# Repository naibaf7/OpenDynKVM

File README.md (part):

<p align="center">
  <picture>
    <source media="(prefers-color-scheme: dark)" srcset="branding/opendynkvm-logo-on-dark.svg">
    
  </picture>
</p>

<h2 align="center">Product page: <a href="https://smartapes.no/opendynkvm/">https://smartapes.no/opendynkvm/</a></h2>

# OpenDynKVM

An open-source USB KVM switch for two PCs that switches in under a millisecond. Each PC is permanently connected to a
keyboard, mouse and aux devices emulated by the KVM ("persistent emulation"), so a switch only changes where the
reports go: no PC sees a disconnect, nothing re-enumerates, and High-Speed USB on the PC side adds about 0.1 ms of
latency. Devices that cannot be emulated (webcams, flash drives) go straight to a PC in passthrough mode. Keyboards
without their own remapping can be remapped on the KVM with the Vial app.

- **Back:** USB-C to PC1, USB-C to PC2, USB-C power/service port (optional power, firmware recovery).
- **Front:** four USB-A ports, Keyboard, Mouse, Aux 1 and Aux 2 (boards before 0.19.0 have three, without Aux 1); a
  mechanical key (tap = switch PC) with an RGB LED; status LEDs per PC and per port.
- **Inside:** an RP2354B (USB host for the front ports, all switching logic), two AT32F405 (one High-Speed USB device per
  PC), three USB 2.0 hubs and a 1:3 analog USB switch per front port but Aux 1, which has no passthrough.

**Status (2026-11-14):** the first boards, hardware 0.12.0, run firmware 0.1.19. Hardware 0.19.0, with the fixes from
their bring-up, a fourth front port and the ESP32-MINI-1 module (2026-11-25), is designed but not ordered yet; one
firmware serves both. What has been verified on a board and what has not:
[DEVELOPMENT.md](DEVELOPMENT.md#bring-up-status).

## Documentation

| | |
|---|---|
| [`specs.md`](specs.md) | What the KVM does, in numbers |
| [`design.md`](design.md) | How the hardware works and why: block diagram, port modes, components, power, PCB |
| [`software.md`](software.md) | How the firmware and the host software work: protocols, updates, Vial, Bluetooth, screen hop |
| [`DEVELOPMENT.md`](DEVELOPMENT.md) | Building the firmware and the host software, changing the board, bring-up status |
| [`hardware/jlcpcb.md`](hardware/jlcpcb.md) | Ordering the board from JLCPCB |
| [`hardware/errata.md`](hardware/errata.md) | Faults of boards already ordered, their workarounds and fixes |
| [`qualified_hardware.md`](qualified_hardware.md) | Mice, keyboards, gamepads and hosts that have been tried, by hardware type |

## Getting a board

There are no boards for sale. The board is ordered assembled from JLCPCB with the files in [`hardware/`](hardware/):
[hardware/jlcpcb.md](hardware/jlcpcb.md) lists every setting of the quote form. Only the MX key switch is plugged into
its socket by hand. The Bluetooth module is optional (boards from 0.16.0): a BOM without it is included. A board
without it can use a small ESP32-C3 board with a USB port (the chip's own, as most have) on a front port instead: the
KVM programs it with the module's firmware when it is new or erased, and that port then serves the wireless hosts
rather than a PC ([software.md §4.13](software.md)).

A 3D-printable case (a tray, a lid with the logo, four spacers and four M3 screws) is in
[`hardware/case/`](hardware/case/), with how to print and assemble it.

## First start of a new board

The chips arrive blank. A USB-C cable is all it takes ([design.md §10](design.md)):

1. Connect a computer to the **PWR/SERVICE** port. A blank RP2354B starts its ROM bootloader and an `RP2350` drive
   appears. (On a board that has firmware, hold the pinhole button while plugging in.)
2. In the app's *Firmware* page, *Set up* (or `odkvmctl update`): it recognises the new board and installs the shipped
   `kvm-first.uf2`. By hand: copy `kvm-first.uf2` (from a release, or built with `cargo xtask dist`) onto the drive.
   The RP2354B restarts with the firmware.
3. It programs both AT32F405s over their SPI links: a few seconds, during which the PC-side hubs are held in reset.
4. The **self-test** runs: one white LED walks along the chain, then for 5 s each LED shows its result, green = passed,
   blinking red = failed (PC LEDs: that PC's link, hub and AT32F405; port LEDs: the port's power switch; key LED: Hub-0
   and the power readings). `odkvmctl status` shows failures in words.
5. Connect PC1 and PC2 to the rear USB-C ports and the devices to the front. Either PC's port can power the KVM, but a
   USB 2.0 port (500 mA) is not enough; a USB-C charger on PWR/SERVICE covers everything ([design.md §6](design.md)).

**Firmware updates** later come from either PC: the *Firmware* page's *Install*, or `odkvmctl update` (both take the
firmware shipped with the app unless given a file or a release's folder), then press the KVM's key when its LED pulses
white. The new image runs on trial and the old one comes back by itself if it fails; the AT32F405s are reprogrammed
automatically when their image changed. A board whose firmware doesn't come up takes the same over PWR/SERVICE: the
pinhole held while plugging in (or `odkvmctl reboot bootloader`), then *Install* on the page's bootloader card, or
`odkvmctl update` with no KVM on a PC port; or copy `kvm-rp2354.uf2` onto the drive by hand.

The app and the firmware go together: a KVM whose firmware is another version than the app's gets only the update
(every page says so, the Firmware page installs the firmware that came with the app, and `odkvmctl` refuses every
command but `update`).

### Install the host software

`opendyn-kvm` (window and tray icon) and `odkvmctl` (command line) control the KVM from either PC.

- **Windows:** run `OpenDynKVM-Setup-<version>.exe`. It installs for the current user, without administrator rights,
  to `%LOCALAPPDATA%\Programs\OpenDynKVM` (both programs are there), with a Start menu entry and an uninstaller under
  Apps. "Start with Windows, in the tray" is ticked by default. The installer is not code-signed yet, so SmartScreen
  asks once ("More info" → "Run anyway").
- **Debian, Ubuntu:** `sudo apt install ./opendyn-kvm_<version>_amd64.deb`.
  **Fedora, openSUSE:** `sudo dnf install ./opendyn-kvm-<version>-1.x86_64.rpm` (or `zypper install`).
  Both install the programs, a menu entry and the udev rule that gives the logged-in user access to the KVM and to the
  monitors' DDC/CI, and load the `i2c-dev` module (now and at every boot).
  The packages are not signed yet. Where RPM refuses unsigned packages ("does not verify: no signature", RPM 6 on
  recent Fedora), install it with `sudo rpm -U --nosignature ./opendyn-kvm-<version>-1.x86_64.rpm`.
- **Start with the system:** Settings → This computer → "Start with the system, in the tray" in `opendyn-kvm` (a
  setting of this computer and user: the Run entry on Windows, `~/.config/autostart` on Linux). `opendyn-kvm --tray`
  starts with the tray icon only; starting the program again while it runs opens its window. On GNOME the tray icon
  needs the AppIndicator extension; without it the window opens instead.
- **From source on Linux**, install the udev rule and the module setting once yourself
  ([DEVELOPMENT.md](DEVELOPMENT.md#build-and-test)).
- **Without a KVM yet:** while none is connected, `opendyn-kvm` offers *Try with a simulated KVM*. Everything acts on
  a made-up KVM, except what doesn't need one: the monitors set up on the Displays page really switch inputs (DDC/CI)
  when the simulated KVM switches, and Screen hop can detect this computer's screens. Monitors set up this way stay
  set up for the real KVM. *Leave the simulator* (or *Use it*, once a KVM is plugged in) goes back to it.

Vial (vial.rocks in the browser, or the Vial app) opens the KVM's Vial interface itself, as the logged-in user. The
packages' udev rule covers it, matched by its interface name "OpenDynKVM Vial" (firmware 0.1.10 on), and opens only that
interface. Without it the interface is root's, and Vial waits at "connecting to device" for good. Vial's own rule
(`59-vial.rules`, from the [Vial manual](https://get.vial.today/manual/linux-udev.html)) works too, matching the KVM by
the `vial:f64c2b3c` in its serial number, but it opens every HID interface of the KVM to the logged-in user, the
keyboard ones included.

Windows needs no drivers.

## Using the KVM

- **Switch PCs:** tap the key on the KVM, double-tap Scroll Lock (the default hotkey, invisible to both PCs), or
  `odkvmctl switch pc1|pc2|toggle`. Keys held during a switch are released on the old PC and stay hidden on the new one
  until you let go.
- **Hotkeys:** a list of up to 16, each an action and its hotkey, on the GUI's Keyboard page (**Add hotkey**, the
  action, the hotkey, **Apply**; × removes one) or with `odkvmctl hotkey`. Out of the box there is one: double-tap
  Scroll Lock toggles the PC. Actions: toggle PC, next / previous host (PC1, PC2, then the Bluetooth hosts that are
  connected), select a host (PC1, PC2, Bluetooth host 1–4), next / previous profile, select a profile (0–7), cycle the
  Aux 2 port's mode. On the command line: `odkvmctl hotkey add select-pc1 ctrl+alt+1`, `odkvmctl hotkey` lists them,
  `odkvmctl hotkey set 2 none`, `odkvmctl hotkey remove 2`. Or press a hotkey instead of typing it: `learn` in place of
  it, or **Learn** on the Keyboard page, then the hotkey on the KVM's keyboard within 10 s. The KVM itself reads the
  keys, so it learns exactly what it will recognise, and they reach neither PC meanwhile (Alt+F4 closes nothing). It
  works from the active PC, with a keyboard in Auto, Normalized or Mirrored mode; one in Passthrough goes straight to
  the PC, so no hotkey works on it.
- **Profiles:** up to eight. A profile sets every device's mode and where its input goes, all at once: the three
  front ports' and the paired Bluetooth devices'. A long press (1 s) on the KVM's key selects the next one. The KVM powers up in profile 0, as it loses power only when both PCs are off; `odkvmctl config set
  remember-profile on` makes it power up in the profile last active. Out of the box, profile 0 *work* runs every port
  in auto (emulated, instant switching) and profile 1 *gaming* runs every port in passthrough (the real devices, about
  1 s per switch). `odkvmctl profile` lists them,
  `odkvmctl profile next|1|gaming` selects one, `odkvmctl profile 1 name games` renames it,
  `odkvmctl profile 1 mouse mirrored` changes a mode, `odkvmctl profile 1 other passthrough pc2` a mode and where it
  goes, and `odkvmctl config set profiles 1-8` sets how many are in use. The GUI has them on the Ports page (a tab per
  profile, a row per device with its mode and where its input goes) and in the sidebar. In passthrough the KVM can't see the keyboard, so the hotkey
  doesn't switch there: use the key or the software.
- **The key's actions:** `odkvmctl config set key-tap|key-long toggle-pc|next-profile|aux2-port|none` and
  `odkvmctl config set long-press-ms 800-3000` (GUI: Keyboard page). By default a tap switches PCs and a 1 s long
  press selects the next profile.
- **Port modes** (`odkvmctl port keyboard|mouse|aux1|aux2 mode <mode>`, which changes the active profile; Aux 1 takes
  every mode but `passthrough`):

  | Mode | What the PCs see | Use it for |
  |---|---|---|
  | `auto` (default) | picks one of the below per device | almost everything |
  | `normalized` | the KVM's own keyboard/mouse | ordinary keyboards and mice; switching is seamless |
  | `mirrored` | the device's own HID interfaces, copied | extra buttons, dials, gamepads |
  | `identity` | as mirrored, plus the device's VID/PID and name | the device maker's own configuration software on the active PC |
  | `passthrough` | the real device on that PC's hub | webcams, storage, firmware updates of a device |
  | `off` | nothing: its input goes nowhere | a device kept plugged in but not wanted in this profile |

  Mirrored devices share 3 USB endpoints, one per HID interface (2 with Vial on). While the keyboard and the mouse
  are both mirrored, the KVM gives up its own keyboard and mouse interfaces for them, and they share 6 (5). A device
  that doesn't fit runs normalized where it can, otherwise passthrough (on Aux 1: off); `odkvmctl status` and the GUI
  say why.

  After swapping the device on a passthrough port, run `odkvmctl port <port> redetect`.
- **Where a device's input goes** (`odkvmctl port <port> route follow|pc1|pc2|host1-host4`, also per profile): by
  default every device follows the active PC or Bluetooth host. Pinned, it types into its host whichever is active:
  a webcam that stays with the work PC, a second keyboard that always goes to the tablet. A pinned keyboard's keys go
  as they are (the keymap and screen hop are the active host's), its hotkeys still work, and its Caps Lock LED is its
  host's. A device in passthrough can be pinned to a PC only.
- **Bluetooth devices** (boards with the module): up to four Bluetooth LE keyboards, mice and other input devices pair
  with the KVM (`odkvmctl device scan`, `odkvmctl device pair 1`, or the GUI's Wireless page: *Look for devices*,
  *Pair*; a keyboard that asks for it gets six digits to type on it). Each is then a device like a front port's, with
  its mode (auto, normalized, off) and routing in every profile, and works with the PCs and the Bluetooth hosts at
  the same time. Bluetooth Classic devices can't pair: the module is Bluetooth LE only.
- **Settings:** `odkvmctl config get`, `odkvmctl config set <name> <value>`, `odkvmctl config save` (they are also saved 5 s
  after the last change), `odkvmctl config reset`. The GUI has the same on its settings page.
- **Software control:** switching and configuration from software can be turned off, from either PC
  (`odkvmctl config set software-switching|software-config off`, or Settings → Software control, after an "are you
  sure"). Turning one back on needs the key on the KVM: ask for it (`… on`, or tick it in the GUI), then tap the key
  within 30 s while its LED pulses white; or hold the key while powering the KVM up, which turns both back on.
- **Diagnostics:** `odkvmctl diag`, or the GUI's Firmware page, shows what the KVM measures: its clocks, voltages,
  temperatures and USB link speeds, each marked good, warning (orange) or bad (red). Hover over a reading in the GUI
  for its limits; *Copy* gives the text for a bug report. Details: [software.md §8.4](software.md).
- **Other:** `odkvmctl watch` (events), `odkvmctl identify` (blink the LEDs), `odkvmctl list` (KVMs this PC sees).
- **PCs off or asleep:**
  - The KVM follows the PC that is on: when the active PC is switched off, the other one becomes active (and the
    monitors follow, if set up below).
  - After 10 s without any PC using it, the KVM goes into standby: LEDs dark, front ports off.
  - While the active PC sleeps, the keyboard and mouse stay powered, and a key press wakes the PC; that key isn't
    typed.
  - A PC that turns on, or a press on the KVM's key, ends standby.
  - Settings: `odkvmctl config set auto-select|standby-wake|standby-glow on|off` (glow: the key LED breathes instead
    of going dark), or in the GUI under Settings. Details: [software.md §4.12](software.md).

The LED colours are described in [design.md §7](design.md).

**Key blinking red:** a part of the KVM doesn't work. The PC LEDs show which side; `odkvmctl status` (or the GUI)
says what, and `odkvmctl diag` shows the readings behind it. If it says the KVM gave up programming a PC-side chip (it
stops after 5 failed attempts in a row, so as not to reprogram it at every power-up), try again with `odkvmctl reboot
at32-retry`, the GUI's "Try again" on the Firmware page, or by holding the key while plugging the KVM in. A Bluetooth
module that needs an update gets it from the app (Firmware or Wireless page) or `odkvmctl update --module`.

### Monitors follow the KVM (DDC/CI)

The KVM switches USB; the monitors can switch along, over DDC/CI from the PC (MCCS VCP 0x60, input source). No video
passes through the KVM.

1. Turn DDC/CI on in each monitor's own menu.
2. In `opendyn-kvm`, **Displays** lists the monitors that answer, with the input each shows now. For each monitor,
   choose the input that shows PC1 and the one that shows PC2. "Use current" takes the input the monitor shows now (for
   this PC); "Show PC1" / "Show PC2" tries one. Inputs the monitor doesn't list can be typed in hex.
3. Then choose, for each of the KVM's profiles, what the monitor does: **follows the KVM**, **stays on PC1**, **stays on
   PC2**, or **not switched**. For example: in *work* both monitors follow, in *gaming* the left one stays on the
   gaming PC and the right one is left alone.
   With the Bluetooth module, each paired host can have an input too (optional), for a laptop or tablet wired to the
   monitor as well: a monitor that follows the KVM shows it while that host has the keyboard and mouse. A host without
   one leaves the monitor on the PC.
4. From then on, every switch (key, hotkey or software) and every change of profile sets those monitors to the input
   they should show; a monitor already right isn't sent anything. It is a setting of this computer and user
   (`~/.config/opendyn-kvm/settings.json`, `%APPDATA%\OpenDynKVM\settings.json`) and works while `opendyn-kvm` runs,
   in the window or the tray. A monitor set up before profiles follows the KVM in every profile.

The KVM tells **both** PCs about every switch and change of profile, so **set each monitor up on one PC** if you can.
The two PCs don't share these settings: a monitor set up on both gets every command twice (some monitors blank for a
moment, or don't answer the second one while they switch), and if the two set-ups differ it follows neither.

One PC is enough when that PC still reaches the monitor while the monitor shows the other PC. Most monitors answer
DDC/CI on every connected input; some only on the one they show. To tell, use "Show PC1" / "Show PC2" to switch the
monitor away from this PC and back. If it doesn't come back, set it up the same way on both PCs (each then switches it
away from itself), or switch it with the monitor's own button. A monitor connected to only one PC can always be switched
from that PC.

`odkvmctl display` lists the monitors (id, inputs, current input); `odkvmctl display input <id> <value>` sets one, for
scripts. On Linux the monitors are found through `/sys/class/drm` (DisplayPort AUX or the connector's DDC bus), on
Windows through the monitor API (dxva2), on macOS through the display's I/O Kit entry (on Apple silicon its AV
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
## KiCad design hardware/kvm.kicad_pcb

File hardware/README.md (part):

# OpenDynKVM hardware

KiCad 10 project for the OpenDynKVM described in [../design.md](../design.md). Every KiCad file here is **generated**:
edit the generator scripts in `tools/`, not the schematic or board in eeschema / pcbnew.

| File | Made by |
|---|---|
| `KVM.kicad_sym` | `tools/gen_symbols.py` (custom symbols: AT32F405CCT7, TS3USB3031, TPS2121, LM66200, TPS2553, SK6812SIDE-A, ESP32-MINI-1) |
| `CustomFootprints.pretty/` | `tools/gen_footprints.py` (TPS2121 RUX, SK6812SIDE-A and the ESP32-MINI-1 from JLC's EasyEDA land patterns, MX switch in a Kailh hot-swap socket, the OpenDynKVM logo as silkscreen from `../branding/`); the HRO USB-C footprint is copied from OpenRower |
| `kvm.kicad_sch` | `tools/gen_schematic.py`: the whole netlist, block by block |
| `kvm.kicad_pcb` | `tools/gen_pcb.py` (placement), then `tools/route.py` (routing, planes) |
| `bom/`, `fab/`, `kvm_gerbers.zip` | `tools/make_fab.py` |
| `kvm_schematic.pdf` | `kicad-cli sch export pdf` |
| `tools/models_3d.json`, `3dmodels/` | `tools/fetch_3d.py`: 3D models for the parts KiCad's 3D library has none for (EasyEDA's, the ones JLC's preview shows) and the MX switch and keycap; the JSON says where each goes on its footprint (`gen_pcb.py` puts them there), the STEP files are a local cache, not in git |
| `render/` | `tools/render_3d.py`: the board raytraced by KiCad, top, bottom and at an angle from the front and the rear; local only, but for `kvm-front-readme.png`, the README's picture (256 colours, at most 256 KB) |
| `case/` | The 3D-printable case: `case/board_facts.py` (KiCad's Python) writes `case/board.json`, `case/gen_case.py` (its own environment: build123d) the STEP and 3MF files ([case/README.md](case/README.md)) |

Checks that run on `kvm.kicad_pcb`: `tools/check_spacing.py` (courtyards, pad gaps, board edges),
`tools/check_aux.py` (every auxiliary passive sits on the side of the chip pin it serves),
`tools/check_copper.py` (copper conflicts, independent of the DRC: clearance between nets on tracks and vias,
dead-end stubs, copper that reaches the same point twice (a doubled route), and per differential pair the line-to-line
gap, skew, via count and stubs) and
`tools/check_usb_si.py` (the same pairs judged *as a channel*: per-lane length and skew in mm and ps, how much of
each link actually runs coupled versus as two single lines, split runs against the documented budgets, paired versus
unpaired vias, the layers used, and long parallel runs beside non-USB copper).

Faults found after ordering, with their workarounds and the fix for the next board: [errata.md](errata.md).

Order diagnostics - the evidence behind [jlcpcb.md](jlcpcb.md); each prints what it measured:
`tools/fab_facts.py` (outline, stack-up, rules, vias and vias in pads, holes, parts at the edges, parts per side),
`tools/zsolve.py [--corners]` (2D field solve of the USB pair on the board's stack-up, with fab tolerances and the
7628 build), `tools/dc_drop.py NET SOURCE SINK=AMPS ...` (DC drop and per-segment current of a power net's copper)
and `tools/jlc_stock.py [--boards N]` (JLC stock and part class for every BOM line; needs network).
`tools/xtal_report.py` reviews every crystal the same way: its chip and load caps, distance and routed length to the
chip's pins, vias and layers, foreign copper in its courtyard and foreign tracks running alongside its nets.

Budgets and accepted exceptions (rev 9, 2026-10-26): the intra-pair skew budget is **1.2 mm = 8 ps** at 6.7 ps/mm
(`check_usb_si.py` `SKEW_MAX`, shared by `check_copper.py` `PAIR_SKEW_MAX`).  That is 0.4 % of a 480 Mb/s bit and about
six times tighter than the ~50 ps USB 2.0 high-speed app notes allow; it was 0.75 mm (5 ps) before, which the two
board-spanning pairs cannot meet (SVC 0.88 mm, H2_AT 0.99 mm).  Up to 0.18.0 Hub-0's disabled port 4 (H0_D4,
strapped) was a documented exception at a 0.1346 mm gap; since 0.19.0 that port is the Aux 1 port's live pair (A1) and
every pair keeps the strict 0.15 mm gap (`check_copper.py` `WAIVED_PAIRS` is empty).

## Regenerating

Run everything from this folder, with uv ([DEVELOPMENT.md](../DEVELOPMENT.md), "Python scripts", sets it up once):

```sh
uv run tools/gen_symbols.py
uv run tools/gen_footprints.py               # needs network for parts not in tools/easyeda_cache/ (a local cache,
                                             # not in git: a fresh clone fetches them once)
uv run tools/gen_schematic.py
kicad-cli sch erc kvm.kicad_sch              # expect 0 violations
kicad-cli sch export netlist --format kicadsexpr -o /tmp/kvm.net kvm.kicad_sch
uv run tools/check_netlist.py /tmp/kvm.net   # the KiCad netlist must equal the generator's pin map, and every USB
                                             # pair keeps D+ on D+ end to end, through the switches (errata.md E1)
uv run tools/gen_pcb.py --force              # --force discards the routing
uv run tools/check_spacing.py                # courtyards, pad gaps, edges
uv run tools/check_aux.py                    # every auxiliary part is on the side of the pin it serves
uv run tools/check_copper.py                  # shorts, stubs, doubled copper, unconnected nets, pair geometry
                                              # under each HS pair (independent of the DRC; passes the committed board)
uv run tools/check_usb_si.py                  # USB as a channel: per-lane length/skew (mm and ps), coupled vs split
                                              # length, split runs vs the documented budgets, paired vias, aggressors
uv run tools/jlc_align.py                    # after adding a part: JLC rotation/offset corrections
uv run tools/route.py --live                 # USB pairs, planes, power, signals (log: tools/route.log);
                                             # --live: watch all layers at http://localhost:8765/
                                             #   the Marks panel lists the router's problem areas (a lane with no
                                             #   way through, where a twist went, where a centre line U-turns);
                                             #   click one to jump to it.  The same spots are in the log.
                                             #   ROUTE_ONLY_PAIRS=H0_MS_DP (comma list of P or N net names)
                                             #   routes that link alone - with --pairs-only about 1.5 min in all
                                             #   instead of 20, same lanes and vias - and ROUTE_DUMP_PAIR=H0_MS_DP
                                             #   (or all) prints its centre runs and both offset lines as they
                                             #   are laid.  Neither changes a full run.
kicad-cli pcb drc --schematic-parity kvm.kicad_pcb
uv run tools/dc_drop.py +5V U402.1,U402.8 U1203=0.5 U1303=0.5 U1702=0.5 U1403=0.5 U403=0.5
                                             # the +5 V feed (jlcpcb.md §5): a full run can pass every check above
                                             # with a bad one (0.15.0's three runs: 495, 121 and 96 mV)
uv run tools/make_fab.py                     # JLC BOM + CPL (corrections applied), gerbers, drill; two assembly
                                             # variants: jlcpcb_*.csv with the Bluetooth module, jlcpcb_*_nobt.csv
                                             # without its parts (Fit = BT, design.md §16)
uv run case/board_facts.py                   # the case: what it needs from the board, into case/board.json
uv run case/gen_case.py                      # then the case itself; it checks the board's parts against it first
uv run tools/fetch_3d.py                     # after adding a part (and jlc_align.py): 3D models KiCad lacks, into
                                             # 3dmodels/ and tools/models_3d.json (network for new ones)
uv run tools/gen_pcb.py --models             # put them on the board; touches nothing else, routed or not
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
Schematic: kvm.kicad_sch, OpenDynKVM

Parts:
C101, C201, C301, C401, C402, C403, C404, C405, C413, C414, C1006, C1106, C1202, C1302, C1402, C1603, C1701, C1801, C1802: 1uF; C_0402_1005Metric; MPN CL05A105KA5NQNC; LCSC C52923
C406, C409, C501, C502, C503, C504, C505, C506, C507, C508, C509, C510, C511, C513, C514, C515, C519, C601, C701, C702, C703, C704, C705, C706, C708, C709, C712, C801, C802, C803, C804, C805, C806, C808, C809, C812, C901, C902, C903, C904, C905, C906, C908, C909, C912, C1001, C1002, C1003, C1004, C1009, C1101, C1102, C1103, C1104, C1109, C1201, C1301, C1401, C1501, C1502, C1503, C1504, C1505, C1506, C1507, C1508, C1509, C1602: 100nF; C_0402_1005Metric; MPN CL05B104KO5NNNC; LCSC C1525
C407, C408, C411, C412, C1601: 22uF; C_0805_2012Metric; MPN CL21A226MAQNNNE; LCSC C45783
C410, C512: 10uF; C_0603_1608Metric; MPN CL10A106KP8NNNC; LCSC C19702
C415, C1203, C1303, C1403, C1702: 220uF; CP_Elec_6.3x7.7; MPN MA10V220M6X8; LCSC C46550458
C516, C707, C807, C907, C1005, C1105: 4.7uF; C_0402_1005Metric; MPN CL05A475MP5NRNC; LCSC C23733
C517, C518, C1007, C1008, C1107, C1108: 15pF; C_0402_1005Metric; MPN 0402CG150J500NT; LCSC C1548
C710, C711, C810, C811, C910, C911: 18pF; C_0402_1005Metric; MPN 0402CG180J500NT; LCSC C1549
D101, D201, D301: PESD5V0S2BT; SOT-23; MPN PESD5V0S2BT,215; LCSC C49338
D102, D202, D302: SMF5.0A; D_SOD-123F; MPN SMF5.0A; LCSC C193402
D1501: SK6812MINI-E; LED_SK6812MINI-E_3.2x2.8mm_P1.5mm_ReverseMount; MPN SK6812MINI-E; LCSC C5149201
D1502: LED PC1; LED_SK6812SIDE-A_4.0x1.6mm; MPN SK6812SIDE-A; LCSC C5378721
D1503: LED KB; LED_SK6812SIDE-A_4.0x1.6mm; MPN SK6812SIDE-A; LCSC C5378721
D1504: LED MS; LED_SK6812SIDE-A_4.0x1.6mm; MPN SK6812SIDE-A; LCSC C5378721
D1505: LED A1; LED_SK6812SIDE-A_4.0x1.6mm; MPN SK6812SIDE-A; LCSC C5378721
D1506: LED A2; LED_SK6812SIDE-A_4.0x1.6mm; MPN SK6812SIDE-A; LCSC C5378721
D1507: LED PC2; LED_SK6812SIDE-A_4.0x1.6mm; MPN SK6812SIDE-A; LCSC C5378721
H1501, H1502, H1503, H1504: M3; MountingHole_3.2mm_M3
J101, J201, J301: USB-C; USB_C_Receptacle_HRO_TYPE-C-31-M-12_Edge; MPN TYPE-C-31-M-12; LCSC C165948
J501: SWD RP2354B; Tag-Connect_TC2030-IDC-NL_2x03_P1.27mm_Vertical
J1001: SWD AT32 #1; Tag-Connect_TC2030-IDC-NL_2x03_P1.27mm_Vertical
J1101: SWD AT32 #2; Tag-Connect_TC2030-IDC-NL_2x03_P1.27mm_Vertical
J1201: USB-A Keyboard; USB_A_Molex_67643_Horizontal; MPN 676430910; LCSC C2798029
J1301: USB-A Mouse; USB_A_Molex_67643_Horizontal; MPN 676430910; LCSC C2798029
J1401: USB-A Aux 2; USB_A_Molex_67643_Horizontal; MPN 676430910; LCSC C2798029
J1701: USB-A Aux 1; USB_A_Molex_67643_Horizontal; MPN 676430910; LCSC C2798029
J1801: EXT; JST_SH_SM04B-SRSS-TB_1x04-1MP_P1.00mm_Horizontal; MPN SM04B-SRSS-TB(LF)(SN); LCSC C160404
L401: 2.2uH; L_Sunlord_SWPA3015S; MPN SWPA3015S2R2MT; LCSC C43389
R101, R102, R201, R202, R301, R302, R1602: 5.1k; R_0402_1005Metric; MPN 0402WGF5101TCE; LCSC C25905
R103, R104, R203, R204, R303, R403, R405, R509, R601, R704, R705, R804, R805, R904, R905, R1201, R1205, R1301, R1305, R1401, R1405, R1703, R1802: 100k; R_0402_1005Metric; MPN 0402WGF1003TCE; LCSC C25741
R304, R404, R409, R411: 47k; R_0402_1005Metric; MPN 0402WGF4702TCE; LCSC C25792
R401, R406, R1203, R1303, R1403, R1701: 22k; R_0402_1005Metric; MPN 0402WGF2202TCE; LCSC C25768
R402, R410, R412, R505, R507, R508, R510, R511, R512, R702, R703, R706, R802, R803, R806, R902, R903, R906, R1001, R1003, R1004, R1005, R1101, R1103, R1104, R1105, R1202, R1204, R1302, R1304, R1402, R1404, R1601, R1702: 10k; R_0402_1005Metric; MPN 0402WGF1002TCE; LCSC C25744
R407: 33k; R_0402_1005Metric; MPN 0402WGF3302TCE; LCSC C25779
R408, R701, R801, R901, R1002, R1102: 12k; R_0402_1005Metric; MPN 0402WGF1202TCE; LCSC C25752
R501, R1501: 33R; R_0402_1005Metric; MPN 0402WGF330JTCE; LCSC C25105
R502, R506, R1603: 1k; R_0402_1005Metric; MPN 0402WGF1001TCE; LCSC C11702
R503, R504: 27R; R_0402_1005Metric; MPN 0402WGF270JTCE; LCSC C25100
R1801: 200k; R_0402_1005Metric; MPN 0402WGF2003TCE; LCSC C25764
R1803, R1804: 4.7k; R_0402_1005Metric; MPN 0402WGF4701TCE; LCSC C25900
R1805, R1806: 100R; R_0402_1005Metric; MPN 0402WGF1000TCE; LCSC C25076
SW501: BOOTSEL; SW_Push_1P1T_XKB_TS-1187A; MPN TS-1187A-B-A-B; LCSC C318884
SW1501: MX key; SW_MX_Hotswap_Kailh_1u; MPN CPG151101S11-2; LCSC C49352235
TP1601: ESP LOG; TestPoint_Pad_D1.0mm
U101, U201, U301, U1201, U1301, U1401, U1701, U1802: USBLC6-2SC6; SOT-23-6; MPN USBLC6-2SC6; LCSC C7519
U401: LM66200; SOT-583-8; MPN LM66200DRLR; LCSC C3235556
U402: TPS2121; TI_RUX0012A_VQFN-HR-12_2x2.5mm_P0.5mm; MPN TPS2121RUXR; LCSC C485916
U403: TLV62569; SOT-23-5; MPN TLV62569DBVR; LCSC C141836
U404: TLV73311; SOT-23-5; MPN TLV73311PDBVR; LCSC C2865431
U501: RP2354B; QFN-80-1EP_10x10mm_P0.4mm_EP3.4x3.4mm; MPN RP2354B; LCSC C39843328
U601, U1202, U1302, U1402: TS3USB3031; Texas_RMG0012A_WQFN-12_1.8x1.8mm_P0.4mm; MPN TS3USB3031RMGR; LCSC C2652459
U701, U801, U901: USB2514B; QFN-36-1EP_6x6mm_P0.5mm_EP3.7x3.7mm; MPN USB2514B-AEZC-TR; LCSC C16251
U1001, U1101: AT32F405CCT7; LQFP-48_7x7mm_P0.5mm; MPN AT32F405CCT7; LCSC C47115471
U1203, U1303, U1403, U1702, U1801: TPS2553; SOT-23-6; MPN TPS2553DBVR; LCSC C55266
U1501: 74AHCT1G125; SOT-23-5; MPN SN74AHCT1G125DBVR; LCSC C7484
U1601: ESP32-MINI-1; MPN ESP32-MINI-1-N4; LCSC C2980305
Y501, Y1001, Y1101: 12MHz; Crystal_SMD_3225-4Pin_3.2x2.5mm; MPN ABM8-272-T3; LCSC C20625731
Y701, Y801, Y901: 24MHz; Crystal_SMD_3225-4Pin_3.2x2.5mm; MPN X322524MOB4SI; LCSC C70590

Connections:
+1V1: C414.1, C513.1, C514.1, C515.1, U404.5 (OUT), U501.10 (DVDD), U501.32 (DVDD), U501.51 (DVDD)
+3V3: C411.1, C412.1, C413.1, C501.1, C502.1, C503.1, C504.1, C505.1, C506.1, C507.1, C508.1, C509.1, C510.1, C511.1, C512.1, C601.1, C701.1, C702.1, C703.1, C704.1, C705.1, C706.1, C707.1, C801.1, C802.1, C803.1, C804.1, C805.1, C806.1, C807.1, C901.1, C902.1, C903.1, C904.1, C905.1, C906.1, C907.1, C1001.1, C1002.1, C1003.1, C1004.1, C1005.1, C1006.1, C1101.1, C1102.1, C1103.1, C1104.1, C1105.1, C1106.1, C1201.1, C1301.1, C1401.1, C1601.1, C1602.1, C1801.1, J501.1 (VCC), J1001.1 (VCC), J1101.1 (VCC), L401.2, R403.1, R405.1, R501.1, R505.1, R510.2, R706.1, R806.1, R905.2, R906.1, R1003.1, R1101.2, R1103.1, R1202.1, R1204.1, R1302.1, R1304.1, R1402.1, R1404.1, R1601.1, R1602.1, R1702.1, U404.1 (IN), U404.3 (EN), U501.5 (IOVDD), U501.15 (IOVDD), U501.24 (IOVDD), U501.29 (IOVDD), U501.41 (IOVDD), U501.50 (IOVDD), U501.59 (ADC_AVDD), U501.60 (IOVDD), U501.68 (USB_OTP_VDD), U501.69 (QSPI_IOVDD), U501.76 (IOVDD), U601.12 (VCC), U701.5 (VDDA33), U701.10 (VDDA33), U701.15 (VDD33), U701.23 (VDD33), U701.29 (VDDA33), U701.36 (VDDA33), U801.5 (VDDA33), U801.10 (VDDA33), U801.15 (VDD33), U801.23 (VDD33), U801.29 (VDDA33), U801.36 (VDDA33), U901.5 (VDDA33), U901.10 (VDDA33), U901.15 (VDD33), U901.23 (VDD33), U901.29 (VDDA33), U901.36 (VDDA33), U1001.1 (VDD), U1001.9 (VDDA), U1001.28 (VDD), U1001.48 (VDD), U1101.1 (VDD), U1101.9 (VDDA), U1101.28 (VDD), U1101.48 (VDD), U1202.12 (VCC), U1302.12 (VCC), U1402.12 (VCC), U1601.3 (3V3), U1801.1 (IN)
+5V: C407.1, C408.1, C409.1, C410.1, C415.1, C1202.1, C1302.1, C1402.1, C1502.1, C1503.1, C1504.1, C1505.1, C1506.1, C1507.1, C1508.1, C1509.1, C1701.1, D1501.3 (VDD), D1502.2 (VDD), D1503.2 (VDD), D1504.2 (VDD), D1505.2 (VDD), D1506.2 (VDD), D1507.2 (VDD), U402.1 (OUT), U402.8 (OUT), U403.1 (EN), U403.4 (VIN), U1203.1 (IN), U1303.1 (IN), U1403.1 (IN), U1501.5 (VCC), U1702.1 (IN)
A1_DM: J1701.2 (D-), U701.8 (USBDM_DN4/PRT_DIS_M4), U1701.1 (I/O1), U1701.6 (I/O1)
A1_DP: J1701.3 (D+), U701.9 (USBDP_DN4/PRT_DIS_P4), U1701.3 (I/O2), U1701.4 (I/O2)
A1_EN: R1703.1, U501.6 (GPIO8), U1702.3 (EN)
A1_FLT: R1702.2, U501.8 (GPIO10), U1702.4 (~FAULT)
A1_ILIM: R1701.1, U1702.5 (ILIM)
A2_DM: J1401.2 (D-), U1401.1 (I/O1), U1401.6 (I/O1), U1402.10 (D-)
A2_DP: J1401.3 (D+), U1401.3 (I/O2), U1401.4 (I/O2), U1402.11 (D+)
A2_EN: R1405.1, U501.40 (GPIO32), U1403.3 (EN)
A2_FLT: R1404.2, U501.42 (GPIO33), U1403.4 (~FAULT)
A2_ILIM: R1403.1, U1403.5 (ILIM)
A2_SEL0: R1401.1, U501.43 (GPIO34), U1402.1 (SEL0)
A2_SEL1: R1402.2, U501.46 (GPIO37), U1402.2 (SEL1)
AT1_BOOT0: R507.1, U501.13 (GPIO14), U1001.44 (PF11/BOOT0)
AT1_CC1: R1004.2, U1001.11 (PA1)
AT1_CC2: R1005.2, U1001.18 (PB0)
AT1_CS: U501.17 (GPIO17), U1001.14 (PA4)
AT1_IRQ: U501.11 (GPIO12), U1001.22 (PB12)
AT1_MISO: U501.16 (GPIO16), U1001.16 (PA6)
AT1_MOSI: U501.19 (GPIO19), U1001.17 (PA7)
AT1_NRST: C1009.1, J1001.3 (~RESET), R1003.2, U501.12 (GPIO13), U1001.7 (NRST)
AT1_ROLE: R1001.1, U1001.2 (PC13)
AT1_RREF: R1002.1, U1001.25 (OTGHS1_R)
AT1_SCK: U501.18 (GPIO18), U1001.15 (PA5)
AT1_SWCLK: J1001.4 (SWCLK), U1001.37 (PA14/SWCLK)
AT1_SWDIO: J1001.2 (SWDIO), U1001.34 (PA13/SWDIO)
AT1_XI: C1007.1, U1001.5 (PF0/HEXT_IN), Y1001.1
AT1_XO: C1008.1, U1001.6 (PF1/HEXT_OUT), Y1001.3
AT2_BOOT0: R508.1, U501.54 (GPIO43/ADC3), U1101.44 (PF11/BOOT0)
AT2_CC1: R1104.2, U1101.11 (PA1)
AT2_CC2: R1105.2, U1101.18 (PB0)
AT2_CS: U501.56 (GPIO45/ADC5), U1101.14 (PA4)
AT2_IRQ: U501.47 (GPIO38), U1101.22 (PB12)
AT2_MISO: U501.55 (GPIO44/ADC4), U1101.16 (PA6)
AT2_MOSI: U501.58 (GPIO47/ADC7), U1101.17 (PA7)
AT2_NRST: C1109.1, J1101.3 (~RESET), R1103.2, U501.48 (GPIO39), U1101.7 (NRST)
AT2_ROLE: R1101.1, U1101.2 (PC13)
AT2_RREF: R1102.1, U1101.25 (OTGHS1_R)
AT2_SCK: U501.57 (GPIO46/ADC6), U1101.15 (PA5)
AT2_SWCLK: J1101.4 (SWCLK), U1101.37 (PA14/SWCLK)
AT2_SWDIO: J1101.2 (SWDIO), U1101.34 (PA13/SWDIO)
AT2_XI: C1107.1, U1101.5 (PF0/HEXT_IN), Y1101.1
AT2_XO: C1108.1, U1101.6 (PF1/HEXT_OUT), Y1101.3
BOOTSEL: R506.2, SW501.2
CC1_PC1: D101.1 (A1), J101.A5 (CC1), R101.1, R1004.1
CC1_PC2: D201.1 (A1), J201.A5 (CC1), R201.1, R1104.1
CC1_PWR: D301.1 (A1), J301.A5 (CC1), R301.1, R511.1
CC2_PC1: D101.2 (A2), J101.B5 (CC2), R102.1, R1005.1
CC2_PC2: D201.2 (A2), J201.B5 (CC2), R202.1, R1105.1
CC2_PWR: D301.2 (A2), J301.B5 (CC2), R302.1, R512.1
CP2: R407.2, R408.1, U402.3 (CP2)
DBG_TX: J501.6 (SWO), U501.45 (GPIO36)
ESP_EN: C1603.1, R1601.2, R1603.2, U1601.8 (EN)
ESP_LOG: TP1601.1, U1601.22 (IO4)
ESP_RST: R1603.1, U501.7 (GPIO9)
ESP_RXD: R1602.2, U501.36 (GPIO28), U1601.21 (IO0), U1601.35 (RXD0/IO3)
ESP_TXD: U501.37 (GPIO29), U1601.36 (TXD0/IO1)
EXT_3V3: C1802.1, J1801.2, R1803.1, R1804.1, U1801.6 (OUT), U1802.5 (VBUS)
EXT_EN: R1802.1, U501.4 (GPIO7), U1801.3 (EN)
EXT_ILIM: R1801.1, U1801.5 (ILIM)
EXT_SCL: J1801.4, R1804.2, R1806.2, U1802.1 (I/O1), U1802.6 (I/O1)
EXT_SCL_RP: R1806.1, U501.2 (GPIO5)
EXT_SDA: J1801.3, R1803.2, R1805.2, U1802.3 (I/O2), U1802.4 (I/O2)
EXT_SDA_RP: R1805.1, U501.1 (GPIO4)
FB_3V3: R405.2, R406.1, U403.5 (FB)
GND: C101.2, C201.2, C301.2, C401.2, C402.2, C403.2, C404.2, C405.2, C406.2, C407.2, C408.2, C409.2, C410.2, C411.2, C412.2, C413.2, C414.2, C415.2, C501.2, C502.2, C503.2, C504.2, C505.2, C506.2, C507.2, C508.2, C509.2, C510.2, C511.2, C512.2, C513.2, C514.2, C515.2, C516.2, C517.2, C518.2, C519.2, C601.2, C701.2, C702.2, C703.2, C704.2, C705.2, C706.2, C707.2, C708.2, C709.2, C710.2, C711.2, C712.2, C801.2, C802.2, C803.2, C804.2, C805.2, C806.2, C807.2, C808.2, C809.2, C810.2, C811.2, C812.2, C901.2, C902.2, C903.2, C904.2, C905.2, C906.2, C907.2, C908.2, C909.2, C910.2, C911.2, C912.2, C1001.2, C1002.2, C1003.2, C1004.2, C1005.2, C1006.2, C1007.2, C1008.2, C1009.2, C1101.2, C1102.2, C1103.2, C1104.2, C1105.2, C1106.2, C1107.2, C1108.2, C1109.2, C1201.2, C1202.2, C1203.2, C1301.2, C1302.2, C1303.2, C1401.2, C1402.2, C1403.2, C1501.2, C1502.2, C1503.2, C1504.2, C1505.2, C1506.2, C1507.2, C1508.2, C1509.2, C1601.2, C1602.2, C1603.2, C1701.2, C1702.2, C1801.2, C1802.2, D101.3 (common), D102.2 (A), D201.3 (common), D202.2 (A), D301.3 (common), D302.2 (A), D1501.1 (VSS), D1502.4 (GND), D1503.4 (GND), D1504.4 (GND), D1505.4 (GND), D1506.4 (GND), D1507.4 (GND), J101.A1 (GND), J101.A12 (GND), J101.B1 (GND), J101.B12 (GND), J101.SH (SHIELD), J201.A1 (GND), J201.A12 (GND), J201.B1 (GND), J201.B12 (GND), J201.SH (SHIELD), J301.A1 (GND), J301.A12 (GND), J301.B1 (GND), J301.B12 (GND), J301.SH (SHIELD), J501.5 (GND), J1001.5 (GND), J1101.5 (GND), J1201.4 (GND), J1201.SH (Shield), J1301.4 (GND), J1301.SH (Shield), J1401.4 (GND), J1401.SH (Shield), J1701.4 (GND), J1701.SH (Shield), J1801.1, J1801.MP (MountPin), R101.2, R102.2, R104.2, R201.2, R202.2, R204.2, R301.2, R302.2, R304.2, R402.2, R404.2, R406.2, R408.2, R410.2, R412.2, R507.2, R508.2, R509.2, R601.2, R701.2, R702.2, R703.2, R704.2, R705.2, R801.2, R802.2, R803.2, R804.2, R805.2, R901.2, R902.2, R903.2, R904.2, R1001.2, R1002.2, R1102.2, R1201.2, R1203.2, R1205.2, R1301.2, R1303.2, R1305.2, R1401.2, R1403.2, R1405.2, R1701.2, R1703.2, R1801.2, R1802.2, SW501.1, SW1501.2, U101.2 (GND), U201.2 (GND), U301.2 (GND), U401.1 (GND), U401.4 (~ON), U401.5 (GND), U402.12 (GND), U403.2 (GND), U404.2 (GND), U501.62 (VREG_PGND), U501.65 (VREG_FB), U501.81 (GND), U601.9 (GND), U701.11 (TEST), U701.37 (VSS), U801.11 (TEST), U801.37 (VSS), U901.11 (TEST), U901.37 (VSS), U1001.8 (VSSA), U1001.23 (VSS), U1001.47 (VSS), U1101.8 (VSSA), U1101.23 (VSS), U1101.47 (VSS), U1201.2 (GND), U1202.9 (GND), U1203.2 (GND), U1301.2 (GND), U1302.9 (GND), U1303.2 (GND), U1401.2 (GND), U1402.9 (GND), U1403.2 (GND), U1501.1, U1501.3 (GND), U1601.1 (GND), U1601.2 (GND), U1601.27 (GND), U1601.38 (GND), U1601.39 (GND), U1601.40 (GND), U1601.41 (GND), U1601.42 (GND), U1601.43 (GND), U1601.44 (GND), U1601.45 (GND), U1601.46 (GND), U1601.47 (GND), U1601.48 (GND), U1601.49 (GND), U1601.50 (GND), U1601.51 (GND), U1601.52 (GND), U1601.53 (GND), U1601.54 (GND), U1601.55 (GND), U1701.2 (GND), U1702.2 (GND), U1801.2 (GND), U1802.2 (GND), Y501.2 (G), Y501.4 (G), Y701.2 (G), Y701.4 (G), Y801.2 (G), Y801.4 (G), Y901.2 (G), Y901.4 (G), Y1001.2 (G), Y1001.4 (G), Y1101.2 (G), Y1101.4 (G)
H0_A2_DM: U701.6 (USBDM_DN3/PRT_DIS_M3), U1402.8 (MHL-)
H0_A2_DP: U701.7 (USBDP_DN3/PRT_DIS_P3), U1402.7 (MHL+)
H0_CFG0: R702.1, U701.24 (SCL/SMBCLK/CFG_SEL0)
H0_CFG1: R703.1, U701.25 (HS_IND/CFG_SEL1)
H0_CRFILT: C708.1, U701.14 (CRFILT)
H0_KB_DM: U701.1 (USBDM_DN1/PRT_DIS_M1), U1202.8 (MHL-)
H0_KB_DP: U701.2 (USBDP_DN1/PRT_DIS_P1), U1202.7 (MHL+)
H0_MS_DM: U701.3 (USBDM_DN2/PRT_DIS_M2), U1302.8 (MHL-)
H0_MS_DP: U701.4 (USBDP_DN2/PRT_DIS_P2), U1302.7 (MHL+)
H0_NR0: R705.1, U701.28 (SUSP_IND/LOCAL_PWR/NON_REM0)
H0_NR1: R704.1, U701.22 (SDA/SMBDATA/NON_REM1)
H0_PLLFILT: C709.1, U701.34 (PLLFILT)
H0_RBIAS: R701.1, U701.35 (RBIAS)
H0_UP_DM: U601.4 (USB1-), U701.30 (USBDM_UP)
H0_UP_DP: U601.3 (USB1+), U701.31 (USBDP_UP)
H0_XI: C710.1, U701.33 (XTALIN/CLKIN), Y701.1
H0_XO: C711.1, U701.32 (XTALOUT), Y701.3
H1_A2_DM: U801.6 (USBDM_DN3/PRT_DIS_M3), U1402.6 (USB2-)
H1_A2_DP: U801.7 (USBDP_DN3/PRT_DIS_P3), U1402.5 (USB2+)
H1_AT_DM: U801.8 (USBDM_DN4/PRT_DIS_M4), U1001.26 (OTGHS1_D-)
H1_AT_DP: U801.9 (USBDP_DN4/PRT_DIS_P4), U1001.27 (OTGHS1_D+)
H1_CFG0: R802.1, U801.24 (SCL/SMBCLK/CFG_SEL0)
H1_CFG1: R803.1, U801.25 (HS_IND/CFG_SEL1)
H1_CRFILT: C808.1, U801.14 (CRFILT)
H1_KB_DM: U801.1 (USBDM_DN1/PRT_DIS_M1), U1202.6 (USB2-)
H1_KB_DP: U801.2 (USBDP_DN1/PRT_DIS_P1), U1202.5 (USB2+)
H1_MS_DM: U801.3 (USBDM_DN2/PRT_DIS_M2), U1302.6 (USB2-)
H1_MS_DP: U801.4 (USBDP_DN2/PRT_DIS_P2), U1302.5 (USB2+)
H1_NR0: R805.1, U801.28 (SUSP_IND/LOCAL_PWR/NON_REM0)
H1_NR1: R804.1, U801.22 (SDA/SMBDATA/NON_REM1)
H1_PLLFILT: C809.1, U801.34 (PLLFILT)
H1_RBIAS: R801.1, U801.35 (RBIAS)
H1_XI: C810.1, U801.33 (XTALIN/CLKIN), Y801.1
H1_XO: C811.1, U801.32 (XTALOUT), Y801.3
H2_A2_DM: U901.8 (USBDM_DN4/PRT_DIS_M4), U1402.4 (USB1-)
H2_A2_DP: U901.9 (USBDP_DN4/PRT_DIS_P4), U1402.3 (USB1+)
H2_AT_DM: U901.1 (USBDM_DN1/PRT_DIS_M1), U1101.26 (OTGHS1_D-)
H2_AT_DP: U901.2 (USBDP_DN1/PRT_DIS_P1), U1101.27 (OTGHS1_D+)
H2_CFG0: R902.1, U901.24 (SCL/SMBCLK/CFG_SEL0)
H2_CFG1: R903.1, U901.25 (HS_IND/CFG_SEL1)
H2_CRFILT: C908.1, U901.14 (CRFILT)
H2_KB_DM: U901.3 (USBDM_DN2/PRT_DIS_M2), U1202.4 (USB1-)
H2_KB_DP: U901.4 (USBDP_DN2/PRT_DIS_P2), U1202.3 (USB1+)
H2_MS_DM: U901.6 (USBDM_DN3/PRT_DIS_M3), U1302.4 (USB1-)
H2_MS_DP: U901.7 (USBDP_DN3/PRT_DIS_P3), U1302.3 (USB1+)
H2_NR0: R905.1, U901.28 (SUSP_IND/LOCAL_PWR/NON_REM0)
H2_NR1: R904.1, U901.22 (SDA/SMBDATA/NON_REM1)
H2_PLLFILT: C909.1, U901.34 (PLLFILT)
H2_RBIAS: R901.1, U901.35 (RBIAS)
H2_XI: C910.1, U901.33 (XTALIN/CLKIN), Y901.1
H2_XO: C911.1, U901.32 (XTALOUT), Y901.3
HUB0_RST: C712.1, R706.2, U501.79 (GPIO2), U701.26 (RESET_N)
HUB0_VBUS: R509.1, U501.80 (GPIO3), U701.27 (VBUS_DET)
HUB1_RST: C812.1, R806.2, U501.3 (GPIO6), U801.26 (RESET_N), U1001.19 (PB1)
HUB2_RST: C912.1, R906.2, U501.44 (GPIO35), U901.26 (RESET_N), U1101.19 (PB1)
ILM: R404.1, U402.10 (ILM)
KB_DM: J1201.2 (D-), U1201.1 (I/O1), U1201.6 (I/O1), U1202.10 (D-)
KB_DP: J1201.3 (D+), U1201.3 (I/O2), U1201.4 (I/O2), U1202.11 (D+)
KB_EN: R1205.1, U501.22 (GPIO22), U1203.3 (EN)
KB_FLT: R1204.2, U501.23 (GPIO23), U1203.4 (~FAULT)
KB_ILIM: R1203.1, U1203.5 (ILIM)
KB_SEL0: R1201.1, U501.20 (GPIO20), U1202.1 (SEL0)
KB_SEL1: R1202.2, U501.21 (GPIO21), U1202.2 (SEL1)
KEY: C1501.1, SW1501.1, U501.9 (GPIO11)
LED_BUF: R1501.1, U1501.4
LED_D0: D1502.1 (DIN), R1501.2
LED_D1: D1502.3 (DOUT), D1503.1 (DIN)
LED_D2: D1503.3 (DOUT), D1504.1 (DIN)
LED_D3: D1504.3 (DOUT), D1505.1 (DIN)
LED_D4: D1505.3 (DOUT), D1506.1 (DIN)
LED_D5: D1506.3 (DOUT), D1507.1 (DIN)
LED_D6: D1501.2 (DIN), D1507.3 (DOUT)
LED_DATA: U501.14 (GPIO15), U1501.2
MS_DM: J1301.2 (D-), U1301.1 (I/O1), U1301.6 (I/O1), U1302.10 (D-)
MS_DP: J1301.3 (D+), U1301.3 (I/O2), U1301.4 (I/O2), U1302.11 (D+)
MS_EN: R1305.1, U501.27 (GPIO26), U1303.3 (EN)
MS_FLT: R1304.2, U501.28 (GPIO27), U1303.4 (~FAULT)
MS_ILIM: R1303.1, U1303.5 (ILIM)
MS_SEL0: R1301.1, U501.25 (GPIO24), U1302.1 (SEL0)
MS_SEL1: R1302.2, U501.26 (GPIO25), U1302.2 (SEL1)
OV1: R409.2, R410.1, U402.5 (OV1)
OV2: R411.2, R412.1, U402.4 (OV2)
PC1_DM: J101.A7 (D-), J101.B7 (D-), U101.1 (I/O1), U101.6 (I/O1), U801.30 (USBDM_UP)
PC1_DP: J101.A6 (D+), J101.B6 (D+), U101.3 (I/O2), U101.4 (I/O2), U801.31 (USBDP_UP)
PC2_DM: J201.A7 (D-), J201.B7 (D-), U201.1 (I/O1), U201.6 (I/O1), U901.30 (USBDM_UP)
PC2_DP: J201.A6 (D+), J201.B6 (D+), U201.3 (I/O2), U201.4 (I/O2), U901.31 (USBDP_UP)
PR1: R401.2, R402.1, U402.6 (PR1)
PWR_ST: R403.2, U402.9 (ST), U501.78 (GPIO1)
QSPI_SS: R506.1, U501.75 (~QSPI_SS)
RP_CC1: R511.2, U501.52 (GPIO41/ADC1)
RP_CC2: R512.2, U501.53 (GPIO42/ADC2)
RP_DM: R504.2, U601.10 (D-)
RP_DP: R503.2, U601.11 (D+)
RP_RUN: C519.1, J501.3 (~RESET), R505.2, U501.35 (RUN)
RP_SWCLK: J501.4 (SWCLK), U501.33 (SWCLK)
RP_SWDIO: J501.2 (SWDIO), U501.34 (SWDIO)
RP_USB_DM_PIN: R504.1, U501.66 (USB_DM)
RP_USB_DP_PIN: R503.1, U501.67 (USB_DP)
RP_VREG: C516.1, R501.2, U501.61 (VREG_AVDD), U501.64 (VREG_VIN)
RP_XIN: C517.1, U501.30 (XIN), Y501.1
RP_XOUT: R502.1, U501.31 (XOUT)
RP_XO_R: C518.1, R502.2, Y501.3
SS: C406.1, U402.11 (SS)
SVC_DM: J301.A7 (D-), J301.B7 (D-), U301.1 (I/O1), U301.6 (I/O1), U601.6 (USB2-)
SVC_DP: J301.A6 (D+), J301.B6 (D+), U301.3 (I/O2), U301.4 (I/O2), U601.5 (USB2+)
SVC_SEL: R510.1, U501.77 (GPIO0), U601.1 (SEL0)
SVC_SEL1: R601.1, U601.2 (SEL1)
SW_3V3: L401.1, U403.3 (SW)
VBUS_A1: C1702.1, J1701.1 (VBUS), U1701.5 (VBUS), U1702.6 (OUT)
VBUS_A2: C1403.1, J1401.1 (VBUS), U1401.5 (VBUS), U1403.6 (OUT)
VBUS_KB: C1203.1, J1201.1 (VBUS), U1201.5 (VBUS), U1203.6 (OUT)
VBUS_MS: C1303.1, J1301.1 (VBUS), U1301.5 (VBUS), U1303.6 (OUT)
VBUS_PC1: C101.1, C402.1, D102.1 (K), J101.A4 (VBUS), J101.A9 (VBUS), J101.B4 (VBUS), J101.B9 (VBUS), R103.1, U101.5 (VBUS), U401.3 (VIN1)
VBUS_PC2: C201.1, C403.1, D202.1 (K), J201.A4 (VBUS), J201.A9 (VBUS), J201.B4 (VBUS), J201.B9 (VBUS), R203.1, U201.5 (VBUS), U401.6 (VIN2)
VBUS_PCS: C401.1, C405.1, R407.1, R411.1, U401.2 (VOUT), U401.7 (VOUT), U402.2 (IN2)
VBUS_PWR: C301.1, C404.1, D302.1 (K), J301.A4 (VBUS), J301.A9 (VBUS), J301.B4 (VBUS), J301.B9 (VBUS), R303.1, R401.1, R409.1, U301.5 (VBUS), U402.7 (IN1)
VDET_PC1: R103.2, R104.1, U801.27 (VBUS_DET), U1001.10 (PA0)
VDET_PC2: R203.2, R204.1, U901.27 (VBUS_DET), U1101.10 (PA0)
VSNS_PWR: R303.2, R304.1, U501.49 (GPIO40/ADC0)

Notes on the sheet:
OpenDynKVM - generated schematic (see design.md)
1. PC1 USB-C (upstream to Hub-1)
2. PC2 USB-C (upstream to Hub-2)
3. PWR / SERVICE USB-C
4. Power path (TPS2121 priority, LM66200 PC OR), 3.3 V buck, 1.1 V LDO
5. RP2354B: USB host + switching logic (core 1.1 V from external LDO, VREG disabled)
6. Service switch: RP2354B USB -> SERVICE port (S=0, default) / Hub-0 (S=1)
7. Hub-0 (KVM host side, FS)
8. Hub-1 (PC1)
9. Hub-2 (PC2)
10. AT32F405 #1 (HS device to PC1)
11. AT32F405 #2 (HS device to PC2)
12. Front port: Keyboard
13. Front port: Mouse
14. Front port: Aux 2
15. MX key + under-key LED (hand-assembled), status LEDs, mounting holes
16. Bluetooth coprocessor ESP32-MINI-1 (fitted on the BT variant only, Fit = BT)
17. Front port: Aux 1 (Hub-0 port 4, normalized / mirrored only)
18. Rear extension connector (JST SH, Qwiic pinout)
Generated by tools/gen_schematic.py from the netlist in that file - edit the generator, not this sheet.
Design rationale: ../design.md. Pin numbers of custom symbols: tools/gen_symbols.py.

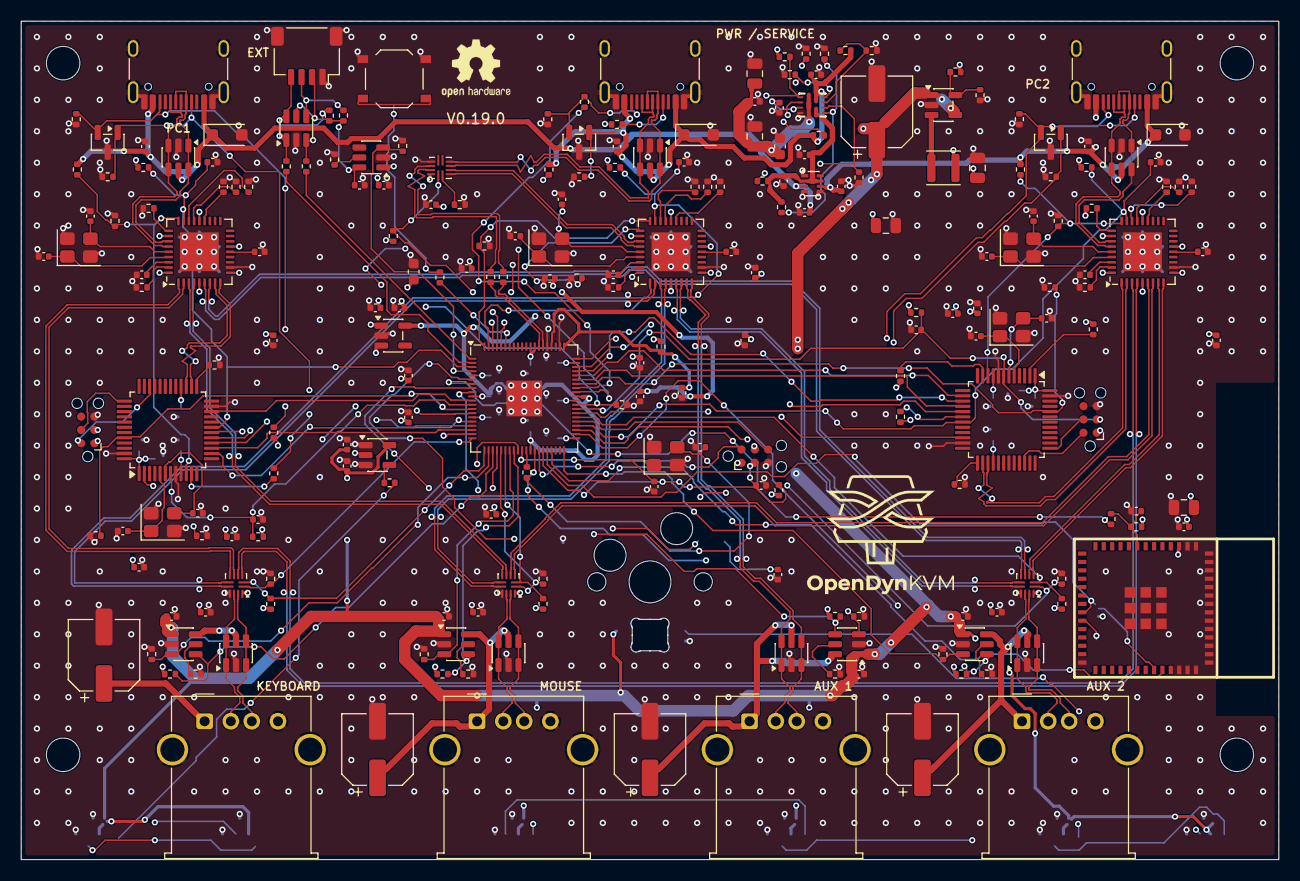
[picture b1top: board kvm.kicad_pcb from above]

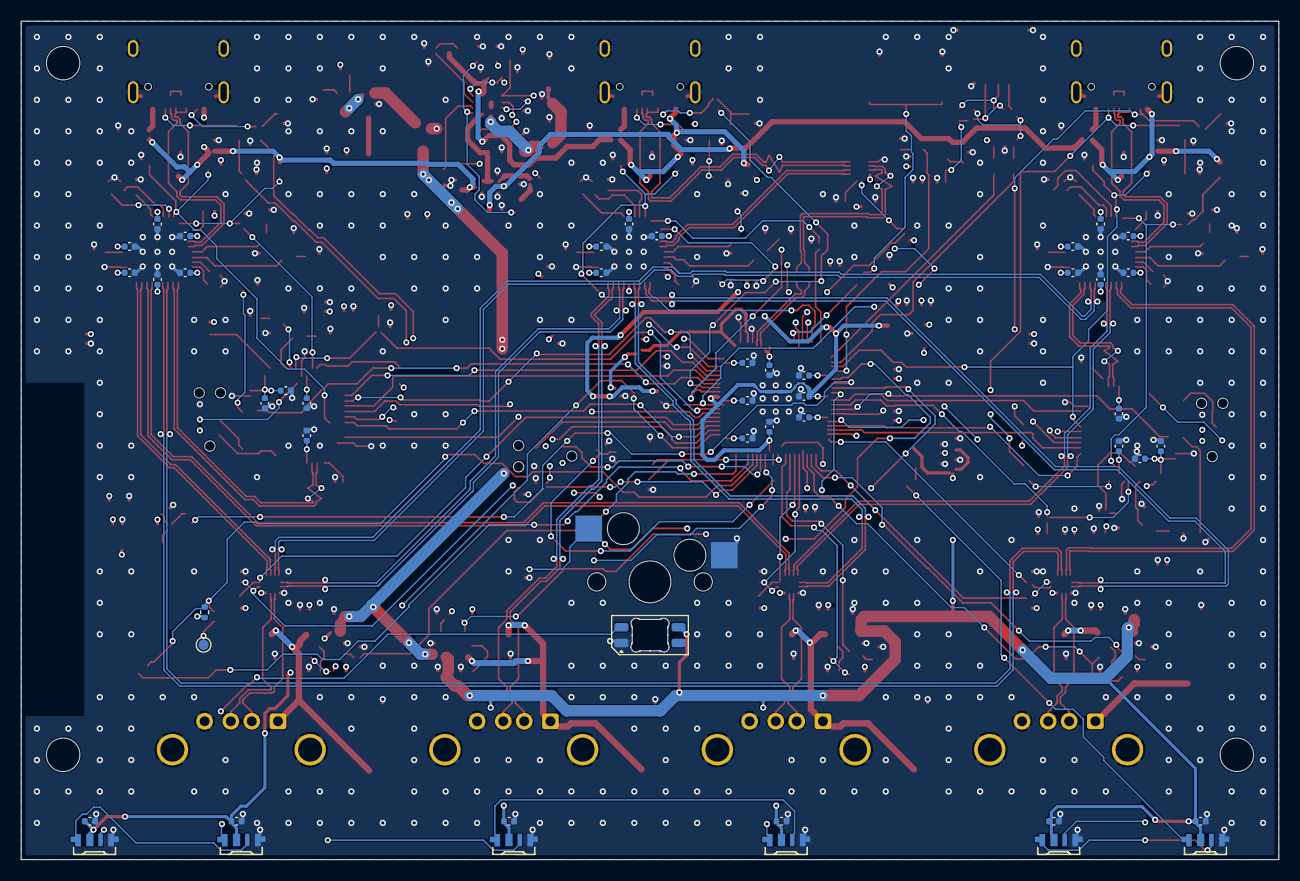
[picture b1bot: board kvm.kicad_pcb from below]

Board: 4 copper layers, 120.0 x 80.0 mm, 279 parts (47 on the bottom side), 187 nets.

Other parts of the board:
LOGO1: OpenDynKVM_Logo_14mm_SilkScreen
LOGO2: OSHW-Logo2_7.3x6mm_SilkScreen

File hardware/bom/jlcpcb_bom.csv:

Comment,Designator,Footprint,LCSC Part #
10uF,"C410,C512",C_0603_1608Metric,C19702
18pF,"C710,C711,C810,C811,C910,C911",C_0402_1005Metric,C1549
100nF,"C406,C409,C501,C502,C503,C504,C505,C506,C507,C508,C509,C510,C511,C513,C514,C515,C519,C601,C701,C702,C703,C704,C705,C706,C708,C709,C712,C801,C802,C803,C804,C805,C806,C808,C809,C812,C901,C902,C903,C904,C905,C906,C908,C909,C912,C1001,C1002,C1003,C1004,C1009,C1101,C1102,C1103,C1104,C1109,C1201,C1301,C1401,C1501,C1502,C1503,C1504,C1505,C1506,C1507,C1508,C1509,C1602",C_0402_1005Metric,C1525
4.7uF,"C516,C707,C807,C907,C1005,C1105",C_0402_1005Metric,C23733
1uF,"C101,C201,C301,C401,C402,C403,C404,C405,C413,C414,C1006,C1106,C1202,C1302,C1402,C1603,C1701,C1801,C1802",C_0402_1005Metric,C52923
15pF,"C517,C518,C1007,C1008,C1107,C1108",C_0402_1005Metric,C1548
220uF,"C415,C1203,C1303,C1403,C1702",CP_Elec_6.3x7.7,C46550458
22uF,"C407,C408,C411,C412,C1601",C_0805_2012Metric,C45783
PESD5V0S2BT,"D101,D201,D301",SOT-23,C49338
SMF5.0A,"D102,D202,D302",D_SOD-123F,C193402
SK6812MINI-E,D1501,LED_SK6812MINI-E_3.2x2.8mm_P1.5mm_ReverseMount,C5149201
LED A1/LED A2/LED KB/LED MS/LED PC1/LED PC2,"D1502,D1503,D1504,D1505,D1506,D1507",LED_SK6812SIDE-A_4.0x1.6mm,C5378721
USB-C,"J101,J201,J301",USB_C_Receptacle_HRO_TYPE-C-31-M-12_Edge,C165948
USB-A Aux 1/USB-A Aux 2/USB-A Keyboard/USB-A Mouse,"J1201,J1301,J1401,J1701",USB_A_Molex_67643_Horizontal,C2798029
EXT,J1801,JST_SH_SM04B-SRSS-TB_1x04-1MP_P1.00mm_Horizontal,C160404
2.2uH,L401,L_Sunlord_SWPA3015S,C43389
5.1k,"R101,R102,R201,R202,R301,R302,R1602",R_0402_1005Metric,C25905
100k,"R103,R104,R203,R204,R303,R403,R405,R509,R601,R704,R705,R804,R805,R904,R905,R1201,R1205,R1301,R1305,R1401,R1405,R1703,R1802",R_0402_1005Metric,C25741
47k,"R304,R404,R409,R411",R_0402_1005Metric,C25792
33k,R407,R_0402_1005Metric,C25779
27R,"R503,R504",R_0402_1005Metric,C25100
10k,"R402,R410,R412,R505,R507,R508,R510,R511,R512,R702,R703,R706,R802,R803,R806,R902,R903,R906,R1001,R1003,R1004,R1005,R1101,R1103,R1104,R1105,R1202,R1204,R1302,R1304,R1402,R1404,R1601,R1702",R_0402_1005Metric,C25744
12k,"R408,R701,R801,R901,R1002,R1102",R_0402_1005Metric,C25752
22k,"R401,R406,R1203,R1303,R1403,R1701",R_0402_1005Metric,C25768
33R,"R501,R1501",R_0402_1005Metric,C25105
1k,"R502,R506,R1603",R_0402_1005Metric,C11702
200k,R1801,R_0402_1005Metric,C25764
4.7k,"R1803,R1804",R_0402_1005Metric,C25900
100R,"R1805,R1806",R_0402_1005Metric,C25076
BOOTSEL,SW501,SW_Push_1P1T_XKB_TS-1187A,C318884
MX key,SW1501,SW_MX_Hotswap_Kailh_1u,C49352235
USBLC6-2SC6,"U101,U201,U301,U1201,U1301,U1401,U1701,U1802",SOT-23-6,C7519
LM66200,U401,SOT-583-8,C3235556
TPS2121,U402,TI_RUX0012A_VQFN-HR-12_2x2.5mm_P0.5mm,C485916
TLV62569,U403,SOT-23-5,C141836
TLV73311,U404,SOT-23-5,C2865431
RP2354B,U501,QFN-80-1EP_10x10mm_P0.4mm_EP3.4x3.4mm,C39843328
USB2514B,"U701,U801,U901",QFN-36-1EP_6x6mm_P0.5mm_EP3.7x3.7mm,C16251
AT32F405CCT7,"U1001,U1101",LQFP-48_7x7mm_P0.5mm,C47115471
TS3USB3031,"U601,U1202,U1302,U1402",Texas_RMG0012A_WQFN-12_1.8x1.8mm_P0.4mm,C2652459
TPS2553,"U1203,U1303,U1403,U1702,U1801",SOT-23-6,C55266
74AHCT1G125,U1501,SOT-23-5,C7484
ESP32-MINI-1,U1601,ESP32-MINI-1,C2980305
24MHz,"Y701,Y801,Y901",Crystal_SMD_3225-4Pin_3.2x2.5mm,C70590
12MHz,"Y501,Y1001,Y1101",Crystal_SMD_3225-4Pin_3.2x2.5mm,C20625731

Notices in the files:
README.md:
Licensing:
- **Hardware:** [CERN-OHL-S v2](LICENSES/CERN-OHL-S-2.0.txt): the board, the scripts that hold its design
(`gen_symbols.py`, `gen_footprints.py`, `gen_schematic.py`, `gen_pcb.py`), the fabrication files and the design
documents. Anyone who makes and distributes boards from a modified design must publish the modified design.
- **Software:** [MIT](LICENSES/MIT.txt) OR [Apache-2.0](LICENSES/Apache-2.0.txt), at your choice: the firmware, the
crates, odkvmctl, xtask, the logo (`branding/`) and their documentation. The general-purpose hardware tools (router,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
